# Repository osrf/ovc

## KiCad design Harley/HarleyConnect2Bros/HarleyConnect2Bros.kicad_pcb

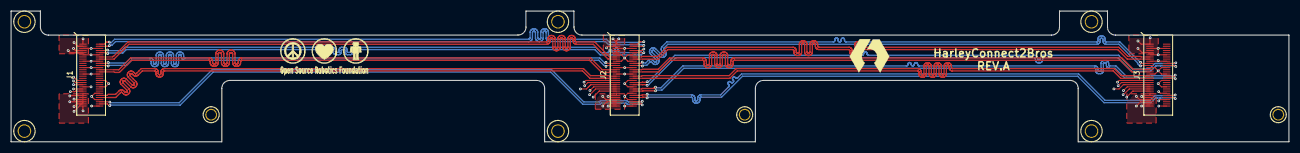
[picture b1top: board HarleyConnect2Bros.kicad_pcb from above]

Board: 6 copper layers, 239.5 x 24.5 mm, 3 parts (0 on the bottom side), 36 nets.

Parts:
J1, J2, J3: DDF40HC(4.0)_60DS_0-4V; DF40HC(4.0)_60DS_0-4V

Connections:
+5V: J1.47, J1.49, J1.51, J1.53, J1.55, J1.57, J1.59, J2.47, J2.49, J2.51, J2.53, J2.55, J2.57, J2.59, J3.47, J3.49, J3.51, J3.53, J3.55, J3.57, J3.59
FPGA_SS_CCLK: J1.35, J2.35, J3.35
FPGA_SS_DIN: J1.37, J2.37, J3.37
FPGA_SS_DONE: J1.43, J2.43, J3.43
FPGA_SS_DOUT: J1.45, J2.45, J3.45
FPGA_SS_INIT_B: J1.39, J2.39, J3.39
FPGA_SS_PROGRAM_B: J1.41, J2.41, J3.41
GND: J1.1, J1.3, J1.5, J1.6, J1.7, J1.9, J1.11, J1.12, J1.17, J1.18, J1.23, J1.24, J1.29, J1.30, J1.36, J1.42, J1.48, J1.54, J1.60, J2.1, J2.3, J2.5, J2.6, J2.7, J2.9, J2.11, J2.12, J2.17, J2.18, J2.23, J2.24, J2.29, J2.30, J2.36, J2.42, J2.48, J2.54, J2.60, J3.1, J3.3, J3.5, J3.6, J3.7, J3.9, J3.11, J3.12, J3.17, J3.18, J3.23, J3.24, J3.29, J3.30, J3.36, J3.42, J3.48, J3.54, J3.60
P_LVDS1+: J1.4, J2.4
P_LVDS1-: J1.2, J2.2
P_LVDS2+: J1.10, J2.10
P_LVDS2-: J1.8, J2.8
P_LVDS3+: J2.16, J3.15
P_LVDS3-: J2.14, J3.13
P_LVDS4+: J2.22, J3.21
P_LVDS4-: J2.20, J3.19
P_LVDS5+: J2.28, J3.27
P_LVDS5-: J2.26, J3.25
P_LVDS6+: J2.34, J3.33
P_LVDS6-: J2.32, J3.31
P_LVDS7+: J2.40, J3.22
P_LVDS7-: J2.38, J3.20
P_LVDS8+: J2.46, J3.34
P_LVDS8-: J2.44, J3.32
P_LVDS9+: J2.52, J3.52
P_LVDS9-: J2.50, J3.50
P_LVDS10+: J1.58, J2.58
P_LVDS10-: J1.56, J2.56
P_LVDS11+: J1.16, J2.15
P_LVDS11-: J1.14, J2.13
P_LVDS12+: J1.22, J2.21
P_LVDS12-: J1.20, J2.19
P_LVDS13+: J1.28, J2.27
P_LVDS13-: J1.26, J2.25
P_LVDS14+: J1.52, J2.33
P_LVDS14-: J1.50, J2.31

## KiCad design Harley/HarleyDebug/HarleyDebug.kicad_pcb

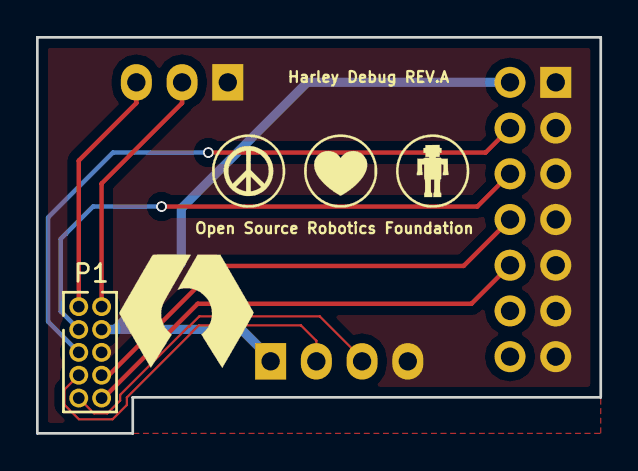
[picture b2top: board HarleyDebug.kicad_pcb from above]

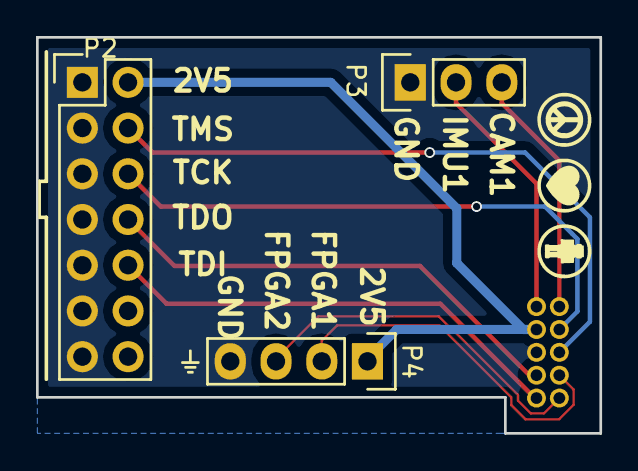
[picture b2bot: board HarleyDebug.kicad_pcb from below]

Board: 2 copper layers, 31.3 x 22.0 mm, 4 parts (3 on the bottom side), 10 nets.

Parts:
P1: CONN_02X05; Pin_Header_Straight_2x05_Pitch1.27mm
P2: CONN_02X07; Pin_Header_Straight_2x07
P3: CONN_01X03; Pin_Header_Straight_1x03
P4: CONN_01X04; Pin_Header_Straight_1x04

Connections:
+2V5: P1.4, P2.2, P4.1
CAM_monitor1: P1.1, P3.3
FPGADebug1: P1.7, P4.2
FPGADebug2: P1.9, P4.3
FPGA_JTAG_TCK: P1.3, P2.6
FPGA_JTAG_TDI: P1.10, P2.10
FPGA_JTAG_TDO: P1.8, P2.8
FPGA_JTAG_TMS: P1.5, P2.4
GND: P1.6, P2.1, P2.3, P2.5, P2.7, P2.9, P2.11, P2.13, P3.1, P4.4
IMU_INT1: P1.2, P3.2

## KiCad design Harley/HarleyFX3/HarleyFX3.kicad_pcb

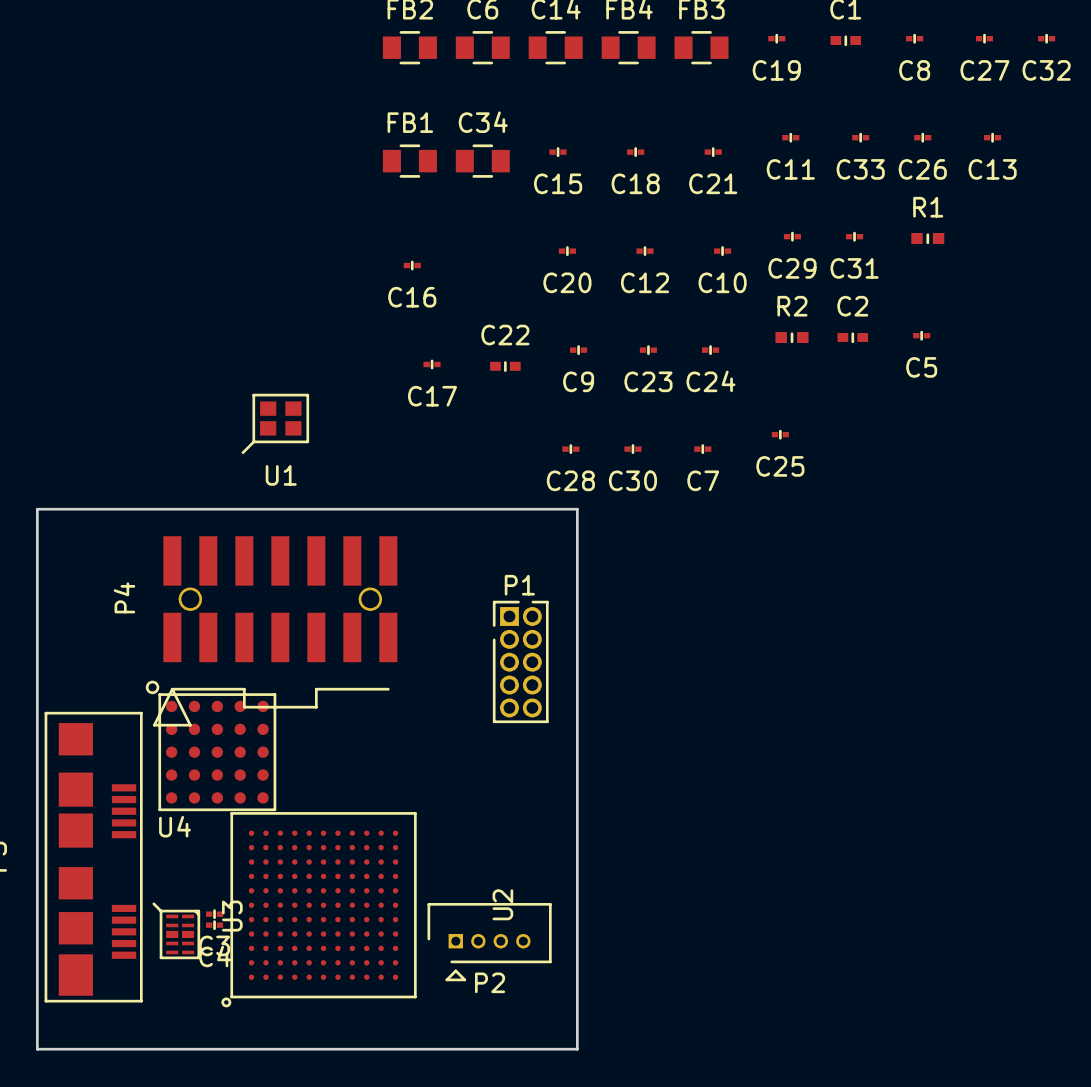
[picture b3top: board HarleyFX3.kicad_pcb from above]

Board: 2 copper layers, 30.0 x 30.0 mm, 48 parts (0 on the bottom side), 25 nets, no tracks yet.

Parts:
C1, C2: 15p; C_0402
C3, C4, C5, C7, C8, C9, C10, C11, C12, C13, C15, C16, C17, C18, C19, C20, C21, C25: 100n; C_0201
C6, C14, C34: 22u; C_0805
C22: 2.2u; C_0402
C23, C24, C26, C27, C28, C29, C30, C31, C32, C33: 10n; C_0201
FB1, FB2, FB3, FB4: 600; C_0805
P1: CONN_02X05; Pin_Header_Straight_2x05_Pitch1.27mm
P2: CONN_01X04; Connector_Molex_PicoBlade_53047-0410
P3: USB_3.1_microB; USB3_Micro-B
P4: Milligrid_02x07; Connector_MilliGrid_02x07_87832-1420
R1: 6.04k; R_0402
R2: 200; R_0402
U1: 8y-19.200MAAE; 8y
U2: CYUSB3014; BGA121C80P11X11_1000X1000X110
U3: IC10pins; 10-UFDFN
U4: LTM4622; LGA25_6.25X6.25X1.82

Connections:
+1V2: C8.1, C10.1, C13.1, C16.1, C18.1, C21.1, C24.1, C27.1, C30.1, C32.1, C34.1, FB1.1, FB2.1, FB3.1, U2.B10, U2.C3, U2.E9, U2.F11, U2.H1, U2.J11, U2.L5, U2.L7
+3V3: C7.1, C9.1, C12.1, C15.1, C17.1, C20.1, C23.1, C26.1, C29.1, C31.1, C33.1, FB4.1, U2.B1, U2.C11, U2.E3, U2.F1, U2.H4, U2.H11, U2.L9
+5V: P2.1, P3.1, U2.E10, U2.E11
/Sheet569FEDF7/AVDDQ: C19.1, C22.1, FB3.2, U2.A7
/Sheet569FEDF7/CVDDQ: C25.1, C28.1, FB4.2, U2.B6
/Sheet569FEDF7/USB_SS_TX+: C4.2, U2.A5
/Sheet569FEDF7/USB_SS_TX-: C3.2, U2.A6
/Sheet569FEDF7/VDDRX: C11.1, C14.1, FB2.2, U2.A2
/Sheet569FEDF7/VDDTX: C5.1, C6.1, FB1.2, U2.B5
FX3_JTAG_TCK: P1.4, U2.F6
FX3_JTAG_TDI: P1.8, U2.E7
FX3_JTAG_TDO: P1.6, U2.C10
FX3_JTAG_TMS: P1.2, U2.E8
FX3_JTAG_TRST: P1.10, U2.B11
GND: C1.2, C2.2, C5.2, C6.2, C7.2, C8.2, C9.2, C10.2, C11.2, C12.2, C13.2, C14.2, C15.2, C16.2, C17.2, C18.2, C19.2, C20.2, C21.2, C22.2, C23.2, C24.2, C25.2, C26.2, C27.2, C28.2, C29.2, C30.2, C31.2, C32.2, C33.2, C34.2, P1.3, P1.5, P1.7, P1.9, P2.4, P3.5, P3.8, P3.SHLD, R1.2, R2.2, U1.2, U1.4, U2.A1, U2.A8, U2.B2, U2.B4, U2.B7, U2.B8, U2.B9, U2.D8, U2.E2, U2.E6, U2.G1, U2.G11, U2.K3, U2.K4, U2.L1, U2.L2, U2.L3, U2.L6, U2.L11, U3.3, U3.8
unnamed: C1.1, U1.3, U2.C7
unnamed: C2.1, U1.1, U2.C6
unnamed: R1.1, U2.C8
unnamed: R2.1, U2.B3
SS_RX+: P3.10, U2.A3, U3.5, U3.6
SS_RX-: P3.9, U2.A4, U3.4, U3.7
SS_TX+: C4.1, P3.7, U3.2, U3.9
SS_TX-: C3.1, P3.6, U3.1, U3.10
USB_HS_D+: P2.3, P3.3, U2.A9
USB_HS_D-: P2.2, P3.2, U2.A10

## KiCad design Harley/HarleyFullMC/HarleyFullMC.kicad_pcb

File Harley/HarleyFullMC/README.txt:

HARLEY-CAM, REV A2
=====================
PCB Fabrication notes:
=====================
* Lead time: 4 days
* Fab quantity: full panel yield (presumably this will be 20 or so?)
* Board outline is a rectangle, 33mm x 45mm = 1.30" x 1.77"
* 10 layers
* micro-vias between the outermost layers (layers 1+2, and layer 9+10). All other vias are through-vias.
* 62 mil PCB thickness
* Copper weights are not critical (everything is relatively low-power). However, impedances are important due to DDR3 and other high-speed traces.
* stackup was started using the included "stackup.pdf" report generated by Sierra's "HDI Stackup Planner" website. We do require the following impedances for these trace widths and layer pairs (+/- 10%)
  * layer 1:  signal, 5mil traces => 50 ohm
  * layer 2:  solid ground plane
  * layer 3:  signal, 5mil traces => 50 ohm
  * layer 4:  signal, 5mil traces => 50 ohm
  * layer 5:  split power planes
  * layer 6:  split power planes
  * layer 7:  some planes and some 5mil traces => 50 ohm
  * layer 8:  signal, 5mil traces => 50 ohm
  * layer 9:  solid ground plane
  * layer 10: signal, 5mil traces => 50 ohm

* Minimum trace/space is 5mil.
* All holes plated
* Minimum via-drill 7 mil, minimum via-pad 13 mil
* Minimum micro-via drill 6 mil, minimum micro-via pad 13 mil
* FR4 material
* HASL finish
* Green soldermask both sides
* White silkscreen both sides

=====================
Assembly notes:
=====================
* Lead time: 4 days
* Assembly quantity: 5 units.
* Double-sided assembly, but all large/heavy parts are on top side.
* U4 is an image sensor. We are not sure about the best practices for them, and defer to Sierra's expertise about whether these parts can be washed.
* RoHS processing is fine but not strictly necessary; these are laboratory prototypes.
* All surface-mount components need to be procured and installed (turnkey).
  * The included BOM provides all distributor and manufacturer part numbers
* Three resistors and three connectors are marked DNP; otherwise, please install all components.

=====================
Shipping notes:
=====================
Please send finished assemblies and extra bare-boards to:

   ATTN: Morgan Quigley
   OSRF
   170 S. Whisman Road
   Bldg. D, Suite A
   Mountain View, CA 94041

Derivatives of this board will be fabricated in higher quantities in the future. DFM feedback is requested. We are just starting to enter the brave new world of HDI and have much to learn.

Designer contact:

Morgan Quigley
morgan@osrfoundation.org
cell: 650-796-4881

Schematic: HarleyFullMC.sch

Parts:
C160: 10n; C_0402; Voltage 6.3; Tolerance 10%
D1: GREEN; LED_0603; Voltage _; Tolerance _
D2: RED; LED_0603; Voltage _; Tolerance _
J3: CONN_01X04; Pin_Header_Straight_1x04_Pitch1.27mm; Voltage _; Tolerance _
J4: CONN_02X05; Pin_Header_Straight_2x05_Pitch1.27mm; Voltage _; Tolerance _
J5: DF40C_60DP_0-4V; Voltage _; Tolerance _
J6: CONN_01X06; GRPB061VWTC; Voltage _; Tolerance _
R17, R18: 10k; C_0201; Voltage _; Tolerance 1%
R20, R22: 200; R_0402; Voltage _; Tolerance 1%
U11: OSCILLATOR; ASDMB; Voltage _; Tolerance _
U12: 24LC128T-I/MNY; 8-TDFN_2x3_1EP; Voltage _; Tolerance _

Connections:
+2V5: C160.1, J4.4, J6.5, R17.1, R18.1, R20.1, R22.1, U11.1 (OE), U11.4 (VDD), U12.8; also elsewhere on the board
+5V: J5.48, J5.50, J5.52, J5.54, J5.56, J5.58, J5.60; also elsewhere on the board
CAM_monitor1: J4.1; also elsewhere on the board
FLASH_SCL: R18.2, U12.6; also elsewhere on the board
FLASH_SDA: R17.2, U12.5; also elsewhere on the board
FPGADebug1: J4.7; also elsewhere on the board
FPGADebug2: J4.9; also elsewhere on the board
FPGA_CLK: U11.3 (Output); also elsewhere on the board
FPGA_JTAG_TCK: J4.3; also elsewhere on the board
FPGA_JTAG_TDI: J4.10; also elsewhere on the board
FPGA_JTAG_TDO: J4.8; also elsewhere on the board
FPGA_JTAG_TMS: J4.5; also elsewhere on the board
FPGA_LED: D2.1; also elsewhere on the board
FPGA_SS_CCLK: J5.36; also elsewhere on the board
FPGA_SS_DIN: J5.38; also elsewhere on the board
FPGA_SS_DONE: J5.44; also elsewhere on the board
FPGA_SS_DOUT: J5.46; also elsewhere on the board
FPGA_SS_INIT_B: J5.40; also elsewhere on the board
FPGA_SS_PROGRAM_B: J5.42; also elsewhere on the board
FX3_JTAG_TCK: J6.1; also elsewhere on the board
FX3_JTAG_TDI: J6.2; also elsewhere on the board
FX3_JTAG_TDO: J6.4; also elsewhere on the board
FX3_JTAG_TMS: J6.3; also elsewhere on the board
FX3_LED/DEBUG: D1.1; also elsewhere on the board
FX3_RST#: J3.2; also elsewhere on the board
FX3_UART_RX: J3.3; also elsewhere on the board
FX3_UART_TX: J3.4; also elsewhere on the board
GND: C160.2, J3.1, J4.6, J5.2, J5.4, J5.5, J5.6, J5.8, J5.10, J5.11, J5.12, J5.17, J5.18, J5.23, J5.24, J5.29, J5.30, J5.35, J5.41, J5.47, J5.53, J5.59, J6.6, U11.2 (GND), U12.3, U12.4, U12.7; also elsewhere on the board
IMU_INT1: J4.2; also elsewhere on the board
unnamed: D1.2, R20.2
unnamed: D2.2, R22.2
P_LVDS1+: J5.3; also elsewhere on the board
P_LVDS1-: J5.1; also elsewhere on the board
P_LVDS2+: J5.9; also elsewhere on the board
P_LVDS2-: J5.7; also elsewhere on the board
P_LVDS3+: J5.15; also elsewhere on the board
P_LVDS3-: J5.13; also elsewhere on the board
P_LVDS4+: J5.21; also elsewhere on the board
P_LVDS4-: J5.19; also elsewhere on the board
P_LVDS5+: J5.27; also elsewhere on the board
P_LVDS5-: J5.25; also elsewhere on the board
P_LVDS6+: J5.33; also elsewhere on the board
P_LVDS6-: J5.31; also elsewhere on the board
P_LVDS7+: J5.39; also elsewhere on the board
P_LVDS7-: J5.37; also elsewhere on the board
P_LVDS8+: J5.45; also elsewhere on the board
P_LVDS8-: J5.43; also elsewhere on the board
P_LVDS9+: J5.51; also elsewhere on the board
P_LVDS9-: J5.49; also elsewhere on the board
P_LVDS10+: J5.57; also elsewhere on the board
P_LVDS10-: J5.55; also elsewhere on the board
P_LVDS11+: J5.16; also elsewhere on the board
P_LVDS11-: J5.14; also elsewhere on the board
P_LVDS12+: J5.22; also elsewhere on the board
P_LVDS12-: J5.20; also elsewhere on the board
P_LVDS13+: J5.28; also elsewhere on the board
P_LVDS13-: J5.26; also elsewhere on the board
P_LVDS14+: J5.34; also elsewhere on the board
P_LVDS14-: J5.32; also elsewhere on the board

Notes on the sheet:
FX3
PowerSupplies
FPGA Banks
DDR3
Imager
IMU
USB3
JTAG/DEBUG
ToNextBiker
Power
CMOS Bank (3V3)
DDR3 Bank (1V35)
Config
Camera LVDS Bank
LVDS to next board Bank
FX3 Bank

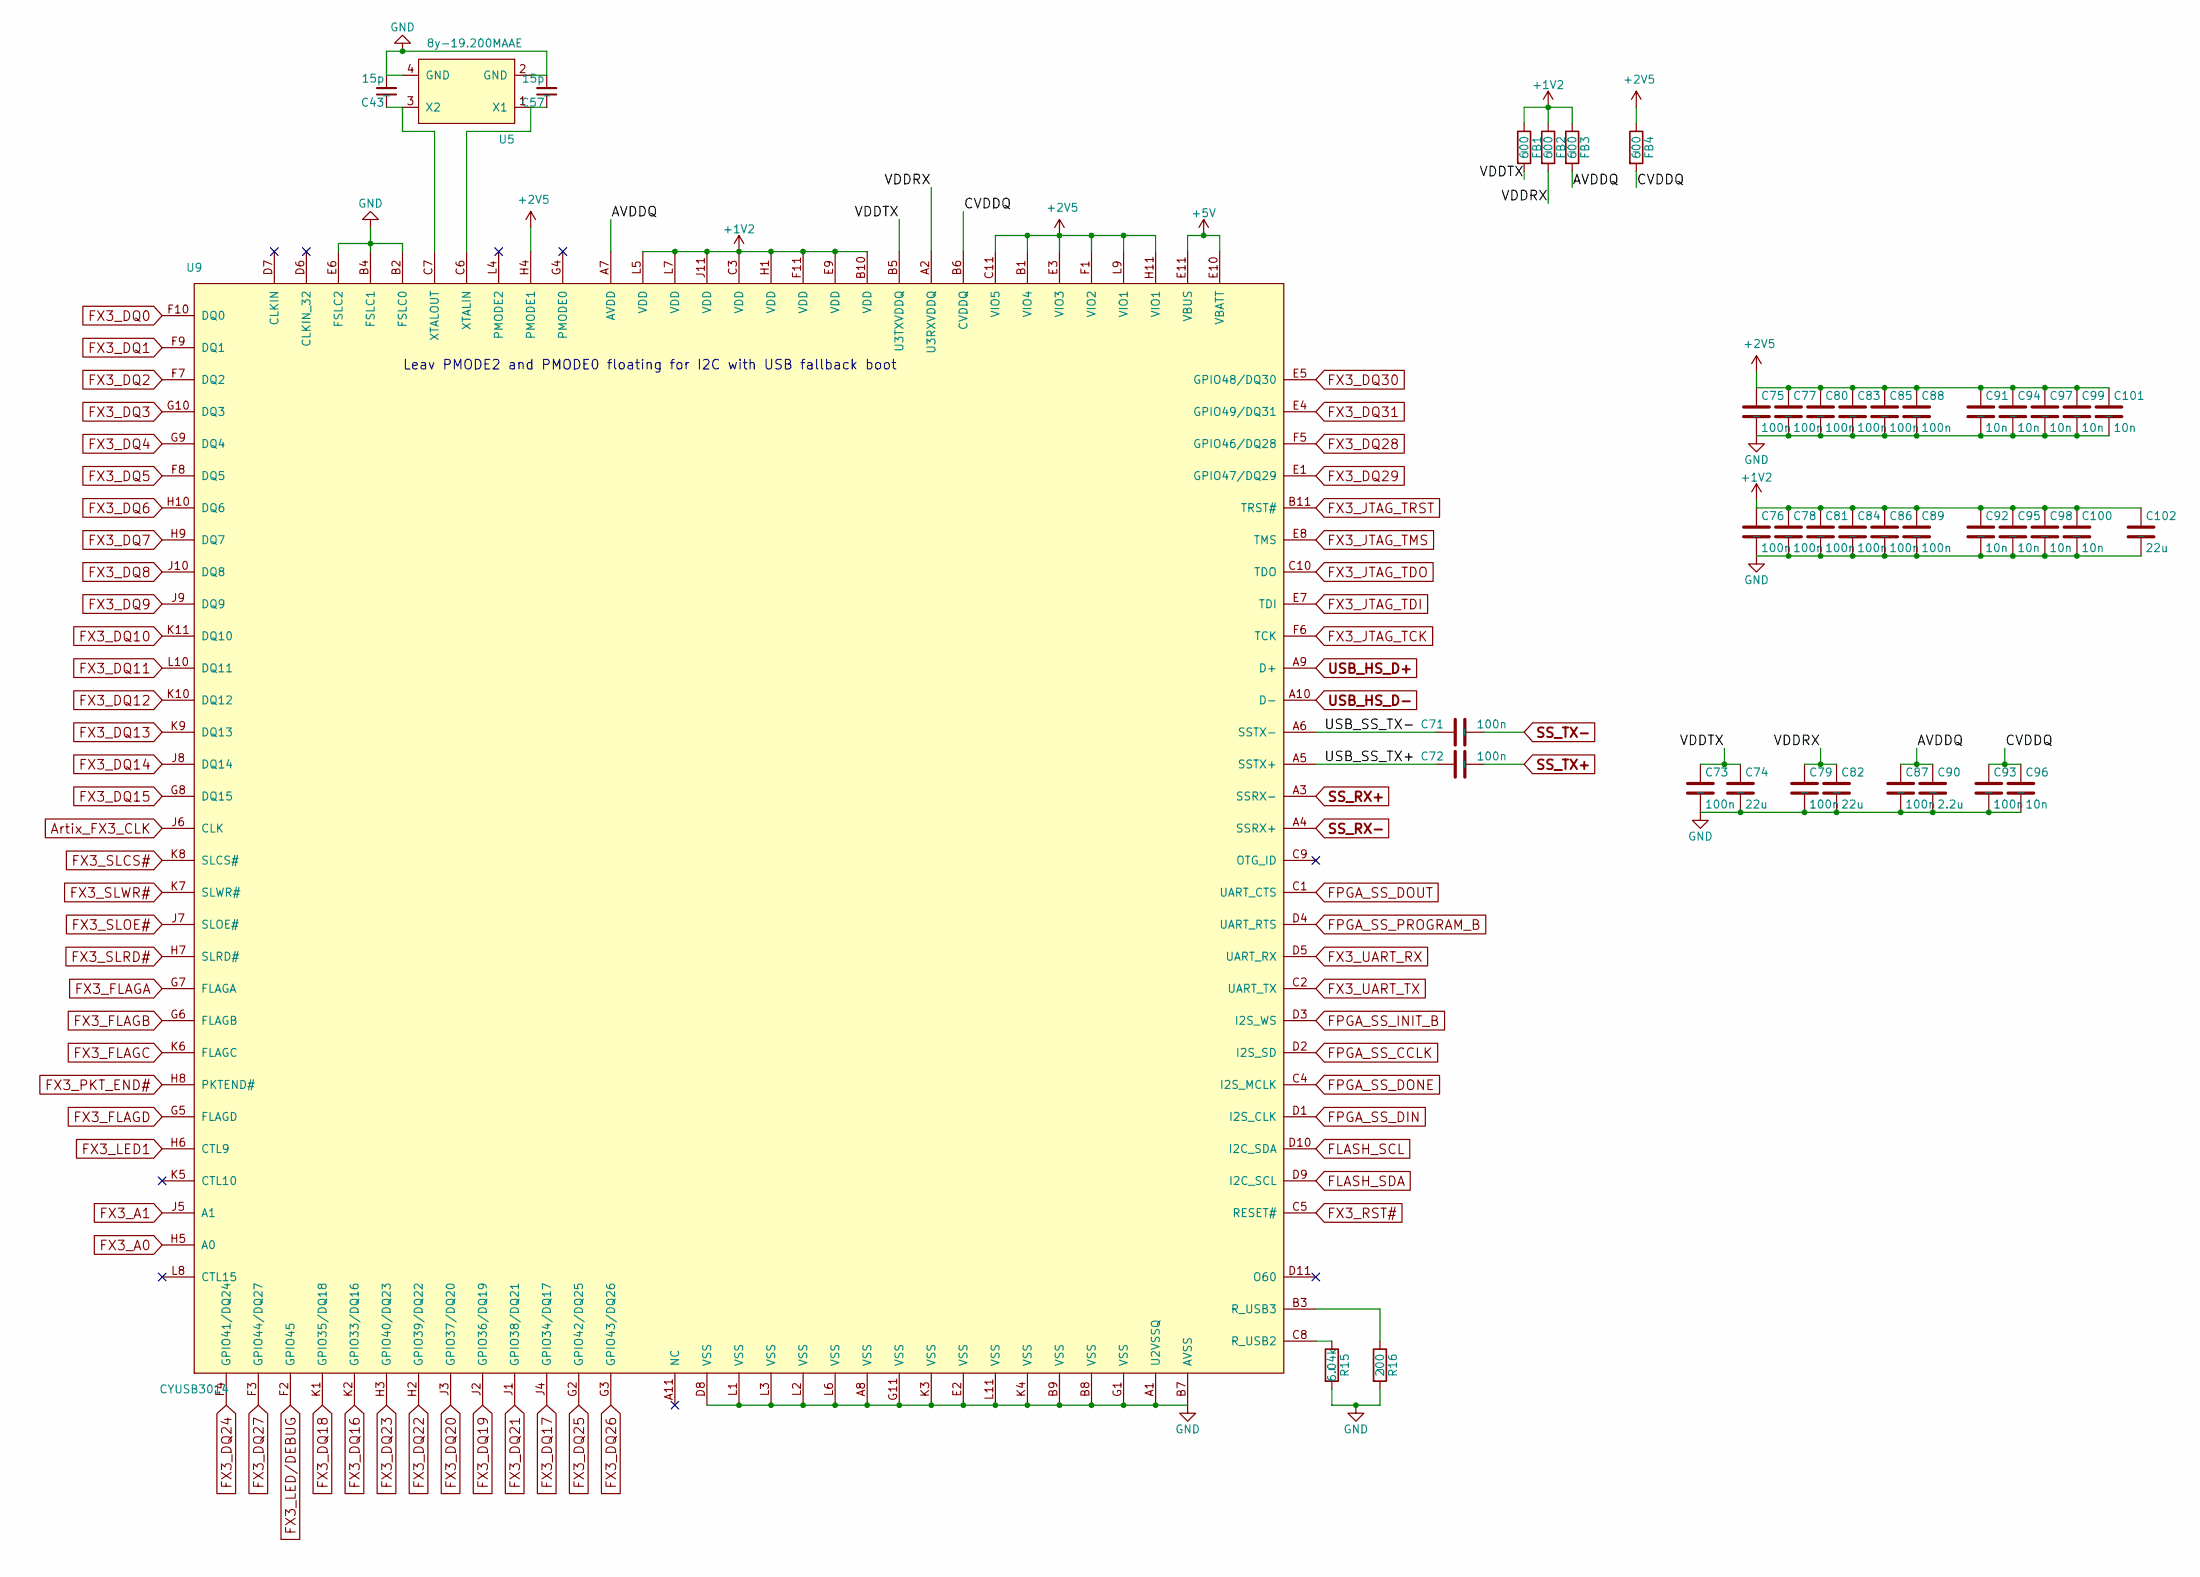
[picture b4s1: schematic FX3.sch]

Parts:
C43, C57: 15p; C_0402; Voltage 50; Tolerance 5%
C71, C72, C73, C75, C76, C77, C78, C79, C80, C81, C83, C84, C85, C86, C87, C88, C89, C93: 100n; C_0201; Voltage 6.3; Tolerance 10%
C74, C82, C102: 22u; C_0805; Voltage 6.3; Tolerance 10%
C90: 2.2u; C_0402; Voltage 6.3; Tolerance 10%
C91, C92, C94, C95, C96, C97, C98, C99, C100, C101: 10n; C_0201; Voltage 10; Tolerance 10%
FB1, FB2, FB3, FB4: 600; C_0805; Voltage _; Tolerance 1%
R15: 6.04k; C_0201; Voltage _; Tolerance 1%
R16: 200; C_0201; Voltage _; Tolerance 1%
U5: 8y-19.200MAAE; 8y; Voltage _; Tolerance _
U9: CYUSB3014; BGA121C80P11X11_1000X1000X110; Voltage _; Tolerance _

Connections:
+1V2: C76.1, C78.1, C81.1, C84.1, C86.1, C89.1, C92.1, C95.1, C98.1, C100.1, C102.1, FB1.1, FB2.1, FB3.1, U9.B10 (VDD), U9.C3 (VDD), U9.E9 (VDD), U9.F11 (VDD), U9.H1 (VDD), U9.J11 (VDD), U9.L5 (VDD), U9.L7 (VDD); also elsewhere on the board
+2V5: C75.1, C77.1, C80.1, C83.1, C85.1, C88.1, C91.1, C94.1, C97.1, C99.1, C101.1, FB4.1, U9.B1 (VIO4), U9.C11 (VIO5), U9.E3 (VIO3), U9.F1 (VIO2), U9.H4 (PMODE1), U9.H11 (VIO1), U9.L9 (VIO1); also elsewhere on the board
+5V: U9.E10 (VBATT), U9.E11 (VBUS); also elsewhere on the board
/Sheet56A15E50/AVDDQ: C87.1, C90.1, FB3.2, U9.A7 (AVDD)
/Sheet56A15E50/CVDDQ: C93.1, C96.1, FB4.2, U9.B6 (CVDDQ)
/Sheet56A15E50/USB_SS_TX+: C72.2, U9.A5 (SSTX+)
/Sheet56A15E50/USB_SS_TX-: C71.2, U9.A6 (SSTX-)
/Sheet56A15E50/VDDRX: C79.1, C82.1, FB2.2, U9.A2 (U3RXVDDQ)
/Sheet56A15E50/VDDTX: C73.1, C74.1, FB1.2, U9.B5 (U3TXVDDQ)
Artix_FX3_CLK: U9.J6 (CLK); also elsewhere on the board
FLASH_SCL: U9.D10 (I2C_SDA); also elsewhere on the board
FLASH_SDA: U9.D9 (I2C_SCL); also elsewhere on the board
FPGA_SS_CCLK: U9.D2 (I2S_SD); also elsewhere on the board
FPGA_SS_DIN: U9.D1 (I2S_CLK); also elsewhere on the board
FPGA_SS_DONE: U9.C4 (I2S_MCLK); also elsewhere on the board
FPGA_SS_DOUT: U9.C1 (UART_CTS); also elsewhere on the board
FPGA_SS_INIT_B: U9.D3 (I2S_WS); also elsewhere on the board
FPGA_SS_PROGRAM_B: U9.D4 (UART_RTS); also elsewhere on the board
FX3_A0: U9.H5 (A0); also elsewhere on the board
FX3_A1: U9.J5 (A1); also elsewhere on the board
FX3_DQ0: U9.F10 (DQ0); also elsewhere on the board
FX3_DQ1: U9.F9 (DQ1); also elsewhere on the board
FX3_DQ2: U9.F7 (DQ2); also elsewhere on the board
FX3_DQ3: U9.G10 (DQ3); also elsewhere on the board
FX3_DQ4: U9.G9 (DQ4); also elsewhere on the board
FX3_DQ5: U9.F8 (DQ5); also elsewhere on the board
FX3_DQ6: U9.H10 (DQ6); also elsewhere on the board
FX3_DQ7: U9.H9 (DQ7); also elsewhere on the board
FX3_DQ8: U9.J10 (DQ8); also elsewhere on the board
FX3_DQ9: U9.J9 (DQ9); also elsewhere on the board
FX3_DQ10: U9.K11 (DQ10); also elsewhere on the board
FX3_DQ11: U9.L10 (DQ11); also elsewhere on the board
FX3_DQ12: U9.K10 (DQ12); also elsewhere on the board
FX3_DQ13: U9.K9 (DQ13); also elsewhere on the board
FX3_DQ14: U9.J8 (DQ14); also elsewhere on the board
FX3_DQ15: U9.G8 (DQ15); also elsewhere on the board
FX3_DQ16: U9.K2 (GPIO33/DQ16); also elsewhere on the board
FX3_DQ17: U9.J4 (GPIO34/DQ17); also elsewhere on the board
FX3_DQ18: U9.K1 (GPIO35/DQ18); also elsewhere on the board
FX3_DQ19: U9.J2 (GPIO36/DQ19); also elsewhere on the board
FX3_DQ20: U9.J3 (GPIO37/DQ20); also elsewhere on the board
FX3_DQ21: U9.J1 (GPIO38/DQ21); also elsewhere on the board
FX3_DQ22: U9.H2 (GPIO39/DQ22); also elsewhere on the board
FX3_DQ23: U9.H3 (GPIO40/DQ23); also elsewhere on the board
FX3_DQ24: U9.F4 (GPIO41/DQ24); also elsewhere on the board
FX3_DQ25: U9.G2 (GPIO42/DQ25); also elsewhere on the board
FX3_DQ26: U9.G3 (GPIO43/DQ26); also elsewhere on the board
FX3_DQ27: U9.F3 (GPIO44/DQ27); also elsewhere on the board
FX3_DQ28: U9.F5 (GPIO46/DQ28); also elsewhere on the board
FX3_DQ29: U9.E1 (GPIO47/DQ29); also elsewhere on the board
FX3_DQ30: U9.E5 (GPIO48/DQ30); also elsewhere on the board
FX3_DQ31: U9.E4 (GPIO49/DQ31); also elsewhere on the board
FX3_FLAGA: U9.G7 (FLAGA); also elsewhere on the board
FX3_FLAGB: U9.G6 (FLAGB); also elsewhere on the board
FX3_FLAGC: U9.K6 (FLAGC); also elsewhere on the board
FX3_FLAGD: U9.G5 (FLAGD); also elsewhere on the board
FX3_JTAG_TCK: U9.F6 (TCK); also elsewhere on the board
FX3_JTAG_TDI: U9.E7 (TDI); also elsewhere on the board
FX3_JTAG_TDO: U9.C10 (TDO); also elsewhere on the board
FX3_JTAG_TMS: U9.E8 (TMS); also elsewhere on the board
FX3_JTAG_TRST: U9.B11 (TRST#)
FX3_LED1: U9.H6 (CTL9)
FX3_LED/DEBUG: U9.F2 (GPIO45); also elsewhere on the board
FX3_PKT_END#: U9.H8 (PKTEND#); also elsewhere on the board
FX3_RST#: U9.C5 (RESET#); also elsewhere on the board
FX3_SLCS#: U9.K8 (SLCS#); also elsewhere on the board
FX3_SLOE#: U9.J7 (SLOE#); also elsewhere on the board
FX3_SLRD#: U9.H7 (SLRD#); also elsewhere on the board
FX3_SLWR#: U9.K7 (SLWR#); also elsewhere on the board
FX3_UART_RX: U9.D5 (UART_RX); also elsewhere on the board
FX3_UART_TX: U9.C2 (UART_TX); also elsewhere on the board
GND: C43.2, C57.2, C73.2, C74.2, C75.2, C76.2, C77.2, C78.2, C79.2, C80.2, C81.2, C82.2, C83.2, C84.2, C85.2, C86.2, C87.2, C88.2, C89.2, C90.2, C91.2, C92.2, C93.2, C94.2, C95.2, C96.2, C97.2, C98.2, C99.2, C100.2, C101.2, C102.2, R15.2, R16.2, U5.2 (GND), U5.4 (GND), U9.A1 (U2VSSQ), U9.A8 (VSS), U9.B2 (FSLC0), U9.B4 (FSLC1), U9.B7 (AVSS), U9.B8 (VSS), U9.B9 (VSS), U9.D8 (VSS), U9.E2 (VSS), U9.E6 (FSLC2), U9.G1 (VSS), U9.G11 (VSS), U9.K3 (VSS), U9.K4 (VSS), U9.L1 (VSS), U9.L2 (VSS), U9.L3 (VSS), U9.L6 (VSS), U9.L11 (VSS); also elsewhere on the board
unnamed: C43.1, U5.3 (X2), U9.C7 (XTALOUT)
unnamed: C57.1, U5.1 (X1), U9.C6 (XTALIN)
unnamed: R15.1, U9.C8 (R_USB2)
unnamed: R16.1, U9.B3 (R_USB3)
SS_RX+: U9.A3 (SSRX-); also elsewhere on the board
SS_RX-: U9.A4 (SSRX+); also elsewhere on the board
SS_TX+: C72.1; also elsewhere on the board
SS_TX-: C71.1; also elsewhere on the board
USB_HS_D+: U9.A9 (D+); also elsewhere on the board
USB_HS_D-: U9.A10 (D-); also elsewhere on the board

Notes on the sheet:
Leav PMODE2 and PMODE0 floating for I2C with USB fallback boot

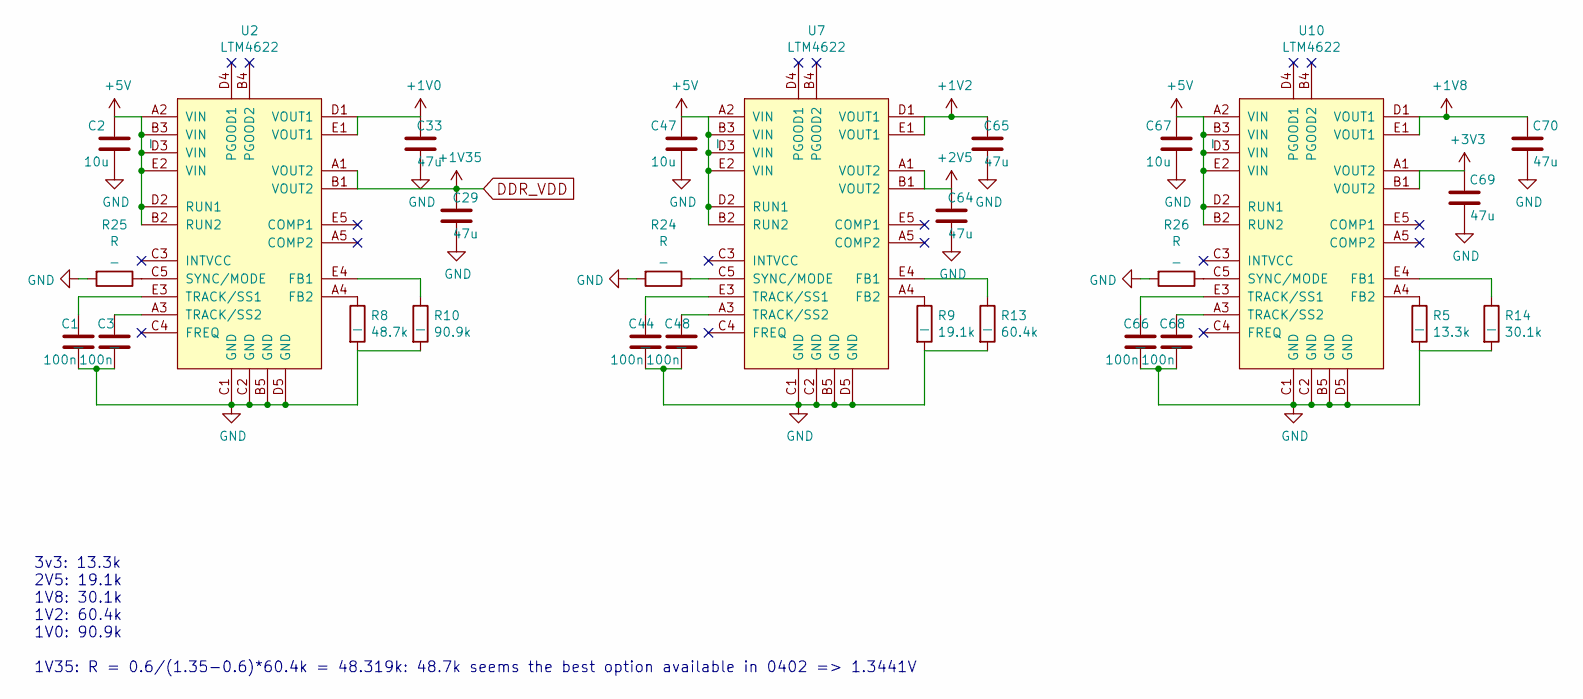
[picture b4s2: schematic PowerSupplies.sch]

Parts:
C1, C3, C44, C48, C66, C68: 100n; C_0402; Voltage 6.3; Tolerance 10%
C2, C47, C67: 10u; C_0603; Voltage 10; Tolerance 10%
C29, C33, C64, C65, C69, C70: 47u; C_0805; Voltage 10; Tolerance 20%
R5: 13.3k; R_0402; Voltage _; Tolerance _
R8: 48.7k; R_0402; Voltage _; Tolerance _
R9: 19.1k; R_0402; Voltage _; Tolerance _
R10: 90.9k; R_0402; Voltage _; Tolerance _
R13: 60.4k; R_0402; Voltage _; Tolerance _
R14: 30.1k; R_0402; Voltage _; Tolerance _
R24, R25, R26: R; C_0201; Voltage _; Tolerance 1%
U2, U7, U10: LTM4622; LGA25_6.25X6.25X1.82; Voltage _; Tolerance _

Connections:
+1V0: C33.2, U2.D1 (VOUT1), U2.E1 (VOUT1); also elsewhere on the board
+1V2: C65.2, U7.D1 (VOUT1), U7.E1 (VOUT1); also elsewhere on the board
+1V8: C70.2, U10.D1 (VOUT1), U10.E1 (VOUT1); also elsewhere on the board
+2V5: C64.2, U7.A1 (VOUT2), U7.B1 (VOUT2); also elsewhere on the board
+3V3: C69.2, U10.A1 (VOUT2), U10.B1 (VOUT2); also elsewhere on the board
+5V: C2.2, C47.2, C67.2, U2.A2 (VIN), U2.B2 (RUN2), U2.B3 (VIN), U2.D2 (RUN1), U2.D3 (VIN), U2.E2 (VIN), U7.A2 (VIN), U7.B2 (RUN2), U7.B3 (VIN), U7.D2 (RUN1), U7.D3 (VIN), U7.E2 (VIN), U10.A2 (VIN), U10.B2 (RUN2), U10.B3 (VIN), U10.D2 (RUN1), U10.D3 (VIN), U10.E2 (VIN); also elsewhere on the board
DDR_VDD: C29.2, U2.A1 (VOUT2), U2.B1 (VOUT2); also elsewhere on the board
GND: C1.2, C2.1, C3.2, C29.1, C33.1, C44.2, C47.1, C48.2, C64.1, C65.1, C66.2, C67.1, C68.2, C69.1, C70.1, R5.2, R8.2, R9.2, R10.2, R13.2, R14.2, R24.2, R25.2, R26.2, U2.B5 (GND), U2.C1 (GND), U2.C2 (GND), U2.D5 (GND), U7.B5 (GND), U7.C1 (GND), U7.C2 (GND), U7.D5 (GND), U10.B5 (GND), U10.C1 (GND), U10.C2 (GND), U10.D5 (GND); also elsewhere on the board
unnamed: C1.1, U2.E3 (TRACK/SS1)
unnamed: C3.1, U2.A3 (TRACK/SS2)
unnamed: C44.1, U7.E3 (TRACK/SS1)
unnamed: C48.1, U7.A3 (TRACK/SS2)
unnamed: C66.1, U10.E3 (TRACK/SS1)
unnamed: C68.1, U10.A3 (TRACK/SS2)
unnamed: R5.1, U10.A4 (FB2)
unnamed: R8.1, U2.A4 (FB2)
unnamed: R9.1, U7.A4 (FB2)
unnamed: R10.1, U2.E4 (FB1)
unnamed: R13.1, U7.E4 (FB1)
unnamed: R14.1, U10.E4 (FB1)
unnamed: R24.1, U7.C5 (SYNC/MODE)
unnamed: R25.1, U2.C5 (SYNC/MODE)
unnamed: R26.1, U10.C5 (SYNC/MODE)

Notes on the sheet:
3v3: 13.3k 2V5: 19.1k 1V8: 30.1k 1V2: 60.4k 1V0: 90.9k 1V35: R = 0.6/(1.35-0.6)*60.4k = 48.319k: 48.7k seems the best option available in 0402 => 1.3441V

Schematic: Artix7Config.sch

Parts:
C116: 470n; C_0201; Voltage 6.3; Tolerance 10%
C118: 47u; C_0805; Voltage 10; Tolerance 20%
C125: 100n; C_0201; Voltage 6.3; Tolerance 10%
FB5, FB6: 600; C_0201; Voltage _; Tolerance _
R19, R21: 4.7k; C_0201; Voltage _; Tolerance 1%
U1: xc7a100tcsg324pkg; BGA324C80P18X18_1500X1500X150; Voltage _; Tolerance _

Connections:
+1V0: U1.F8, U1.F10, U1.G7, U1.G9, U1.G11, U1.H8, U1.J7, U1.J11, U1.K8, U1.L7, U1.L11, U1.M8, U1.M10, U1.N7, U1.N9, U1.N11; also elsewhere on the board
+1V8: FB6.1, U1.F12, U1.H12, U1.K12, U1.M12; also elsewhere on the board
+2V5: C118.1, R19.1, R21.1, U1.A17, U1.C13, U1.D16, U1.G15, U1.H18, U1.K4, U1.K14, U1.L17, U1.N3, U1.N13, U1.P6, U1.P8, U1.P11, U1.P12, U1.P13, U1.P16, U1.R9, U1.T2, U1.T12, U1.U5, U1.U15, U1.V8, U1.V18; also elsewhere on the board
+3V3: U1.B10; also elsewhere on the board
/Sheet56A15EBD/GND_ADC: FB5.1, U1.H9, U1.J9, U1.K10
Artix_FX3_CLK: U1.P3; also elsewhere on the board
CAM_CLK_IN+: U1.B13; also elsewhere on the board
CAM_CLK_IN-: U1.B14; also elsewhere on the board
CAM_CLK_OUT+: U1.F15; also elsewhere on the board
CAM_CLK_OUT-: U1.F16; also elsewhere on the board
CAM_CLK_PLL: U1.C10; also elsewhere on the board
CAM_DOUT0+: U1.A11; also elsewhere on the board
CAM_DOUT0-: U1.B11; also elsewhere on the board
CAM_DOUT1+: U1.A14; also elsewhere on the board
CAM_DOUT1-: U1.A13; also elsewhere on the board
CAM_DOUT2+: U1.A16; also elsewhere on the board
CAM_DOUT2-: U1.A15; also elsewhere on the board
CAM_DOUT3+: U1.B17; also elsewhere on the board
CAM_DOUT3-: U1.B16; also elsewhere on the board
CAM_RST#: U1.B9; also elsewhere on the board
CAM_SS#: U1.A8; also elsewhere on the board
CAM_SYNC+: U1.B18; also elsewhere on the board
CAM_SYNC-: U1.A18; also elsewhere on the board
CAM_monitor0: U1.A10; also elsewhere on the board
CAM_trigger0: U1.D10; also elsewhere on the board
CAM_trigger1: U1.D9; also elsewhere on the board
DDR_A0: U1.G2; also elsewhere on the board
DDR_A1: U1.H5; also elsewhere on the board
DDR_A2: U1.G3; also elsewhere on the board
DDR_A3: U1.H2; also elsewhere on the board
DDR_A4: U1.J4; also elsewhere on the board
DDR_A5: U1.J2; also elsewhere on the board
DDR_A6: U1.G6; also elsewhere on the board
DDR_A7: U1.K1; also elsewhere on the board
DDR_A8: U1.H6; also elsewhere on the board
DDR_A9: U1.J3; also elsewhere on the board
DDR_A10: U1.F6; also elsewhere on the board
DDR_A11: U1.H4; also elsewhere on the board
DDR_A12: U1.G4; also elsewhere on the board
DDR_A13: U1.K2; also elsewhere on the board
DDR_BA0: U1.E1; also elsewhere on the board
DDR_BA1: U1.G1; also elsewhere on the board
DDR_BA2: U1.F1; also elsewhere on the board
DDR_CAS#: U1.C1; also elsewhere on the board
DDR_CKE: U1.H1; also elsewhere on the board
DDR_CLK+: U1.F4; also elsewhere on the board
DDR_CLK-: U1.F3; also elsewhere on the board
DDR_DQL0: U1.B7; also elsewhere on the board
DDR_DQL1: U1.D8; also elsewhere on the board
DDR_DQL2: U1.C7; also elsewhere on the board
DDR_DQL3: U1.B6; also elsewhere on the board
DDR_DQL4: U1.E5; also elsewhere on the board
DDR_DQL5: U1.D7; also elsewhere on the board
DDR_DQL6: U1.E6; also elsewhere on the board
DDR_DQL7: U1.E7; also elsewhere on the board
DDR_DQSL+: U1.A6; also elsewhere on the board
DDR_DQSL-: U1.A5; also elsewhere on the board
DDR_DQSU+: U1.B1; also elsewhere on the board
DDR_DQSU-: U1.A1; also elsewhere on the board
DDR_DQU0: U1.B2; also elsewhere on the board
DDR_DQU1: U1.D4; also elsewhere on the board
DDR_DQU2: U1.B3; also elsewhere on the board
DDR_DQU3: U1.D5; also elsewhere on the board
DDR_DQU4: U1.B4; also elsewhere on the board
DDR_DQU5: U1.C4; also elsewhere on the board
DDR_DQU6: U1.A3; also elsewhere on the board
DDR_DQU7: U1.A4; also elsewhere on the board
DDR_ODT: U1.E2; also elsewhere on the board
DDR_RAS#: U1.C2; also elsewhere on the board
DDR_RST#: U1.J5; also elsewhere on the board
DDR_VDD: U1.A7, U1.C3, U1.D6, U1.F2, U1.G5, U1.J1; also elsewhere on the board
DDR_WE#: U1.D2; also elsewhere on the board
FPGADebug1: U1.C16; also elsewhere on the board
FPGADebug2: U1.F14; also elsewhere on the board
FPGA_CLK: U1.N5; also elsewhere on the board
FPGA_JTAG_TCK: U1.E10; also elsewhere on the board
FPGA_JTAG_TDI: U1.E11; also elsewhere on the board
FPGA_JTAG_TDO: U1.E13; also elsewhere on the board
FPGA_JTAG_TMS: U1.E12; also elsewhere on the board
FPGA_LED: U1.C17; also elsewhere on the board
FPGA_SS_CCLK: U1.E9; also elsewhere on the board
FPGA_SS_DIN: U1.K18; also elsewhere on the board
FPGA_SS_DONE: U1.P10; also elsewhere on the board
FPGA_SS_DOUT: U1.T16; also elsewhere on the board
FPGA_SS_INIT_B: R19.2, U1.P7; also elsewhere on the board
FPGA_SS_PROGRAM_B: R21.2, U1.P9; also elsewhere on the board
FX3_A0: U1.T9; also elsewhere on the board
FX3_A1: U1.R11; also elsewhere on the board
FX3_DQ0: U1.V7; also elsewhere on the board
FX3_DQ1: U1.R3; also elsewhere on the board
FX3_DQ2: U1.R2; also elsewhere on the board
FX3_DQ3: U1.V4; also elsewhere on the board
FX3_DQ4: U1.T4; also elsewhere on the board
FX3_DQ5: U1.T3; also elsewhere on the board
FX3_DQ6: U1.V9; also elsewhere on the board
FX3_DQ7: U1.U6; also elsewhere on the board
FX3_DQ8: U1.V10; also elsewhere on the board
FX3_DQ9: U1.V11; also elsewhere on the board
FX3_DQ10: U1.U11; also elsewhere on the board
FX3_DQ11: U1.U13; also elsewhere on the board
FX3_DQ12: U1.V12; also elsewhere on the board
FX3_DQ13: U1.V14; also elsewhere on the board
FX3_DQ14: U1.T10; also elsewhere on the board
FX3_DQ15: U1.T5; also elsewhere on the board
FX3_DQ16: U1.U16; also elsewhere on the board
FX3_DQ17: U1.U12; also elsewhere on the board
FX3_DQ18: U1.V17; also elsewhere on the board
FX3_DQ19: U1.T14; also elsewhere on the board
FX3_DQ20: U1.V16; also elsewhere on the board
FX3_DQ21: U1.P14; also elsewhere on the board
FX3_DQ22: U1.R12; also elsewhere on the board
FX3_DQ23: U1.T11; also elsewhere on the board
FX3_DQ24: U1.P5; also elsewhere on the board
FX3_DQ25: U1.T13; also elsewhere on the board
FX3_DQ26: U1.R8; also elsewhere on the board
FX3_DQ27: U1.L14; also elsewhere on the board
FX3_DQ28: U1.U4; also elsewhere on the board
FX3_DQ29: U1.P18; also elsewhere on the board
FX3_DQ30: U1.V1; also elsewhere on the board
FX3_DQ31: U1.R16; also elsewhere on the board
FX3_FLAGA: U1.V6; also elsewhere on the board
FX3_FLAGB: U1.U9; also elsewhere on the board
FX3_FLAGC: U1.T15; also elsewhere on the board
FX3_FLAGD: U1.T8; also elsewhere on the board
FX3_PKT_END#: U1.R5; also elsewhere on the board
FX3_SLCS#: U1.U14; also elsewhere on the board
FX3_SLOE#: U1.R10; also elsewhere on the board
FX3_SLRD#: U1.R6; also elsewhere on the board
FX3_SLWR#: U1.V15; also elsewhere on the board
GND: C116.2, C118.2, C125.2, FB5.2, U1.A2, U1.A12, U1.B5, U1.B15, U1.C8, U1.C18, U1.D1, U1.D11, U1.E4, U1.E8, U1.E14, U1.F7, U1.F9, U1.F11, U1.F17, U1.G8, U1.G10, U1.G12, U1.H3, U1.H7, U1.H11, U1.H13, U1.J6, U1.J8, U1.J10, U1.J12, U1.J16, U1.K7, U1.K9, U1.K11, U1.L2, U1.L8, U1.L9, U1.L10, U1.L12, U1.M5, U1.M7, U1.M9, U1.M11, U1.M15, U1.N8, U1.N10, U1.N12, U1.N18, U1.P1, U1.R4, U1.R14, U1.T7, U1.T17, U1.U10, U1.V3, U1.V13; also elsewhere on the board
IMU_SS#: U1.C11; also elsewhere on the board
unnamed: C116.1, C125.1, FB6.2, U1.H10
P_LVDS1+: U1.E18; also elsewhere on the board
P_LVDS1-: U1.D18; also elsewhere on the board
P_LVDS2+: U1.G18; also elsewhere on the board
P_LVDS2-: U1.F18; also elsewhere on the board
P_LVDS3+: U1.J17; also elsewhere on the board
P_LVDS3-: U1.J18; also elsewhere on the board
P_LVDS4+: U1.H16; also elsewhere on the board
P_LVDS4-: U1.G16; also elsewhere on the board
P_LVDS5+: U1.H14; also elsewhere on the board
P_LVDS5-: U1.G14; also elsewhere on the board
P_LVDS6+: U1.M18; also elsewhere on the board
P_LVDS6-: U1.L18; also elsewhere on the board
P_LVDS7+: U1.L15; also elsewhere on the board
P_LVDS7-: U1.L16; also elsewhere on the board
P_LVDS8+: U1.N15; also elsewhere on the board
P_LVDS8-: U1.N16; also elsewhere on the board
P_LVDS9+: U1.T18; also elsewhere on the board
P_LVDS9-: U1.R18; also elsewhere on the board
P_LVDS10+: U1.U17; also elsewhere on the board
P_LVDS10-: U1.U18; also elsewhere on the board
P_LVDS11+: U1.D17; also elsewhere on the board
P_LVDS11-: U1.E17; also elsewhere on the board
P_LVDS12+: U1.R17; also elsewhere on the board
P_LVDS12-: U1.P17; also elsewhere on the board
P_LVDS13+: U1.R15; also elsewhere on the board
P_LVDS13-: U1.P15; also elsewhere on the board
P_LVDS14+: U1.M13; also elsewhere on the board
P_LVDS14-: U1.L13; also elsewhere on the board
SPI_MISO: U1.A9; also elsewhere on the board
SPI_MOSI: U1.C9; also elsewhere on the board
SPI_SCK: U1.B8; also elsewhere on the board
